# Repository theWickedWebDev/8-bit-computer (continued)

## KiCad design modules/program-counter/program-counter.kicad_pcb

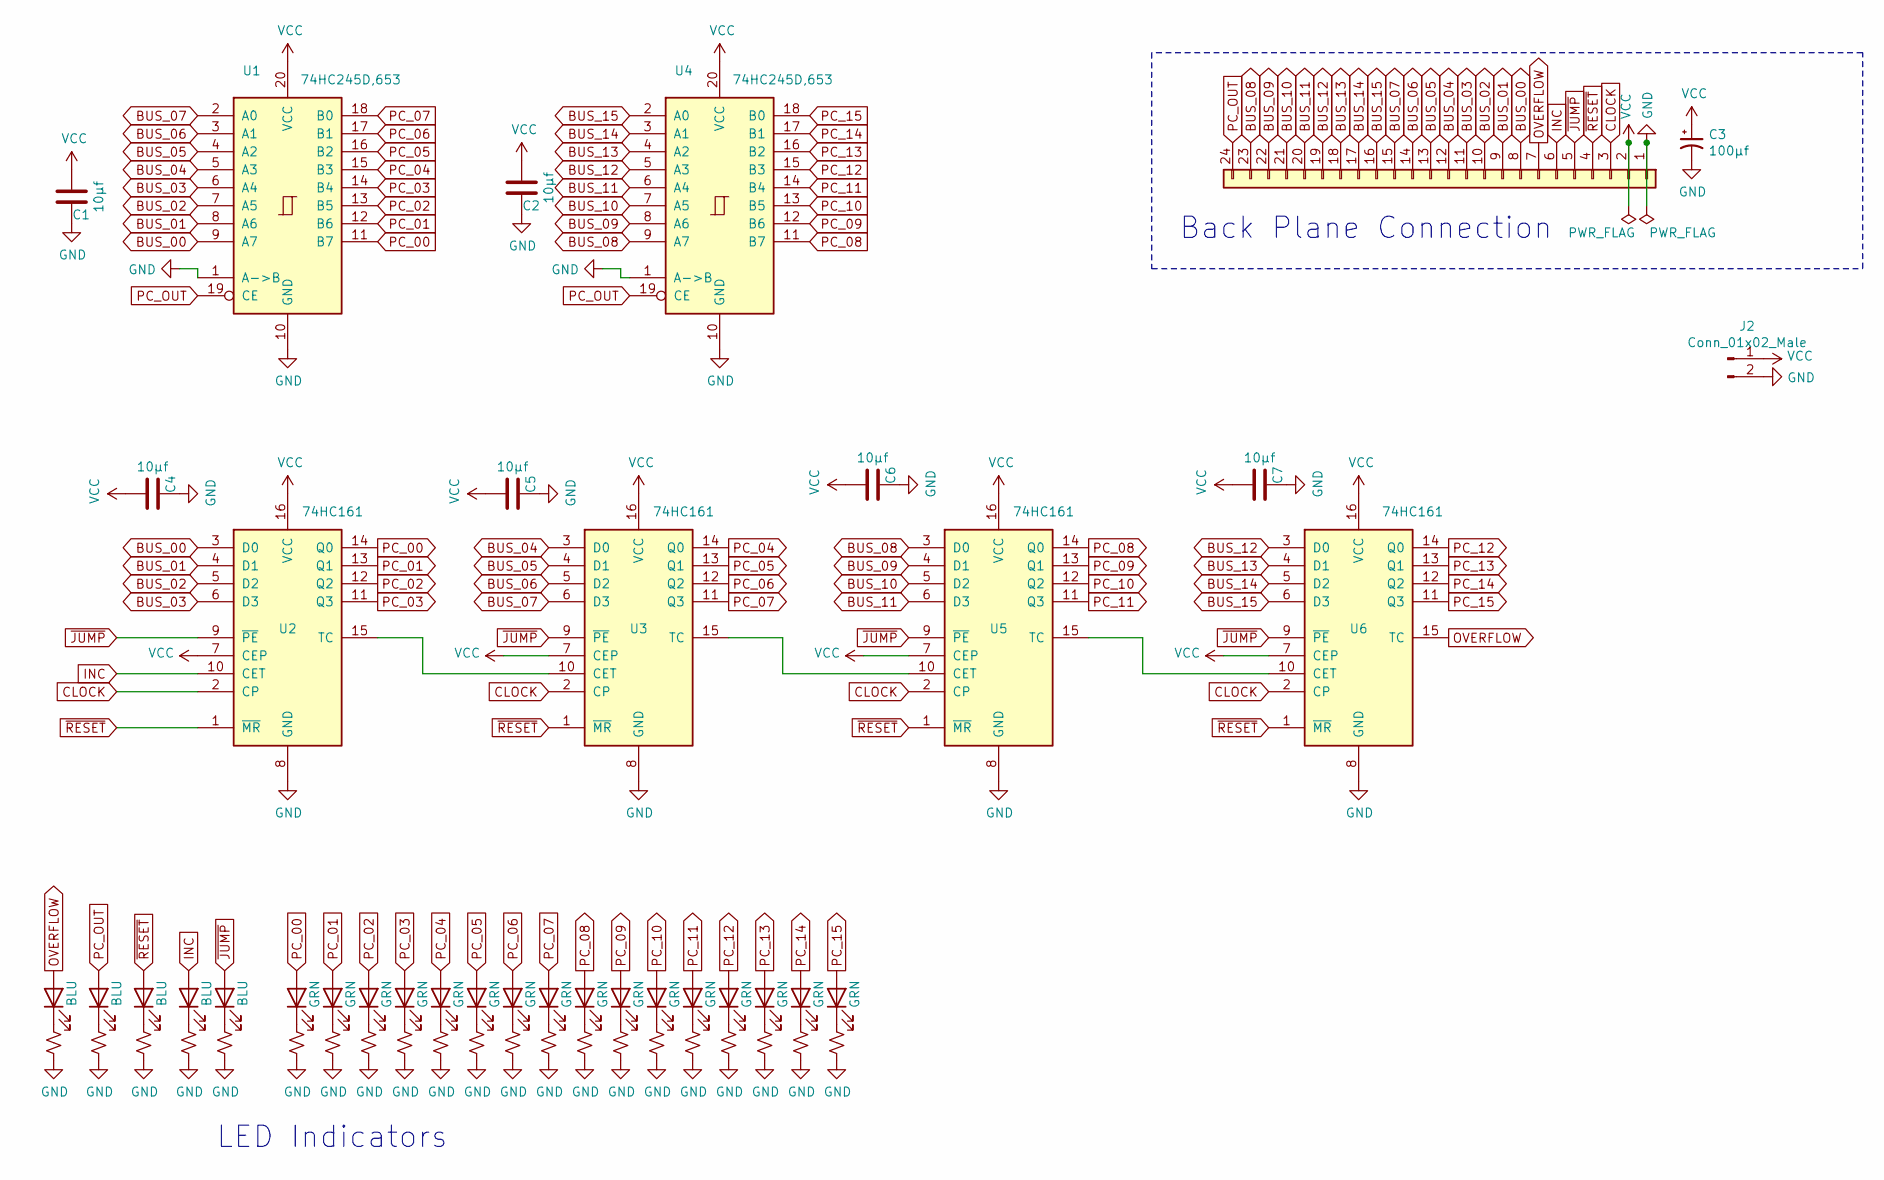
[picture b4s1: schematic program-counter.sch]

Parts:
C1, C2, C4, C5, C6, C7: CL05A106MQ5NUNC; C_0402_1005Metric; JLCPCB C15525
C3: SMD-ECAP-5x5.8; CP_Elec_5x5.8; JLCPCB C140924
D1, D2, D3, D4, D21: 19-217/BHC-ZL1M2RY/3T; LED_0603_1608Metric; JLCPCB C72041
D5, D6, D7, D8, D9, D10, D11, D12, D13, D14, D15, D16, D17, D18, D19, D20: 19-217/GHC-YR1S2/3T; LED_0603_1608Metric; JLCPCB C72043
J1: Conn_01x24; PinHeader_1x24_P2.54mm_Vertical
J2: Conn_01x02_Male; PinHeader_1x02_P2.54mm_Vertical
R1, R2, R3, R4, R5, R6, R7, R8, R9, R10, R11, R12, R13, R14, R15, R16, R17, R18, R19, R20, R21: 0402WGF1001TCE; R_0402_1005Metric; JLCPCB C11702
U1, U4: 74HC245D,653; SO-20_12.8x7.5mm_P1.27mm; JLCPCB C5625
U2, U3, U5, U6: SN74HC161DR; SOIC-16_3.9x9.9mm_P1.27mm

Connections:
BUS_00: J1.8, U1.9 (A7), U2.3 (D0)
BUS_01: J1.9, U1.8 (A6), U2.4 (D1)
BUS_02: J1.10, U1.7 (A5), U2.5 (D2)
BUS_03: J1.11, U1.6 (A4), U2.6 (D3)
BUS_04: J1.12, U1.5 (A3), U3.3 (D0)
BUS_05: J1.13, U1.4 (A2), U3.4 (D1)
BUS_06: J1.14, U1.3 (A1), U3.5 (D2)
BUS_07: J1.15, U1.2 (A0), U3.6 (D3)
BUS_08: J1.23, U4.9 (A7), U5.3 (D0)
BUS_09: J1.22, U4.8 (A6), U5.4 (D1)
BUS_10: J1.21, U4.7 (A5), U5.5 (D2)
BUS_11: J1.20, U4.6 (A4), U5.6 (D3)
BUS_12: J1.19, U4.5 (A3), U6.3 (D0)
BUS_13: J1.18, U4.4 (A2), U6.4 (D1)
BUS_14: J1.17, U4.3 (A1), U6.5 (D2)
BUS_15: J1.16, U4.2 (A0), U6.6 (D3)
CLOCK: J1.3, U2.2 (CP), U3.2 (CP), U5.2 (CP), U6.2 (CP)
GND: C1.2, C2.2, C3.2, C4.2, C5.2, C6.2, C7.2, J1.1, J2.2, R1.2, R2.2, R3.2, R4.2, R5.2, R6.2, R7.2, R8.2, R9.2, R10.2, R11.2, R12.2, R13.2, R14.2, R15.2, R16.2, R17.2, R18.2, R19.2, R20.2, R21.2, U1.1 (A->B), U1.10 (GND), U2.8 (GND), U3.8 (GND), U4.1 (A->B), U4.10 (GND), U5.8 (GND), U6.8 (GND)
INC: D3.2 (A), J1.6, U2.10 (CET)
unnamed: D1.1 (K), R1.1
unnamed: D2.1 (K), R2.1
unnamed: D3.1 (K), R3.1
unnamed: D4.1 (K), R4.1
unnamed: D5.1 (K), R5.1
unnamed: D6.1 (K), R6.1
unnamed: D7.1 (K), R7.1
unnamed: D8.1 (K), R8.1
unnamed: D9.1 (K), R9.1
unnamed: D10.1 (K), R10.1
unnamed: D11.1 (K), R11.1
unnamed: D12.1 (K), R12.1
unnamed: D13.1 (K), R13.1
unnamed: D14.1 (K), R14.1
unnamed: D15.1 (K), R15.1
unnamed: D16.1 (K), R16.1
unnamed: D17.1 (K), R17.1
unnamed: D18.1 (K), R18.1
unnamed: D19.1 (K), R19.1
unnamed: D20.1 (K), R20.1
unnamed: D21.1 (K), R21.1
unnamed: U2.15 (TC), U3.10 (CET)
unnamed: U3.15 (TC), U5.10 (CET)
unnamed: U5.15 (TC), U6.10 (CET)
OVERFLOW: D21.2 (A), J1.7, U6.15 (TC)
PC_00: D5.2 (A), U1.11 (B7), U2.14 (Q0)
PC_01: D6.2 (A), U1.12 (B6), U2.13 (Q1)
PC_02: D7.2 (A), U1.13 (B5), U2.12 (Q2)
PC_03: D8.2 (A), U1.14 (B4), U2.11 (Q3)
PC_04: D9.2 (A), U1.15 (B3), U3.14 (Q0)
PC_05: D10.2 (A), U1.16 (B2), U3.13 (Q1)
PC_06: D11.2 (A), U1.17 (B1), U3.12 (Q2)
PC_07: D12.2 (A), U1.18 (B0), U3.11 (Q3)
PC_08: D13.2 (A), U4.11 (B7), U5.14 (Q0)
PC_09: D14.2 (A), U4.12 (B6), U5.13 (Q1)
PC_10: D15.2 (A), U4.13 (B5), U5.12 (Q2)
PC_11: D16.2 (A), U4.14 (B4), U5.11 (Q3)
PC_12: D17.2 (A), U4.15 (B3), U6.14 (Q0)
PC_13: D18.2 (A), U4.16 (B2), U6.13 (Q1)
PC_14: D19.2 (A), U4.17 (B1), U6.12 (Q2)
PC_15: D20.2 (A), U4.18 (B0), U6.11 (Q3)
PC_OUT: D2.2 (A), J1.24, U1.19 (CE), U4.19 (CE)
VCC: C1.1, C2.1, C3.1, C4.1, C5.1, C6.1, C7.1, J1.2, J2.1, U1.20 (VCC), U2.7 (CEP), U2.16 (VCC), U3.7 (CEP), U3.16 (VCC), U4.20 (VCC), U5.7 (CEP), U5.16 (VCC), U6.7 (CEP), U6.16 (VCC)
~JUMP: D4.2 (A), J1.5, U2.9 (~PE), U3.9 (~PE), U5.9 (~PE), U6.9 (~PE)
~RESET: D1.2 (A), J1.4, U2.1 (~MR), U3.1 (~MR), U5.1 (~MR), U6.1 (~MR)

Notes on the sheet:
Back Plane Connection
LED Indicators

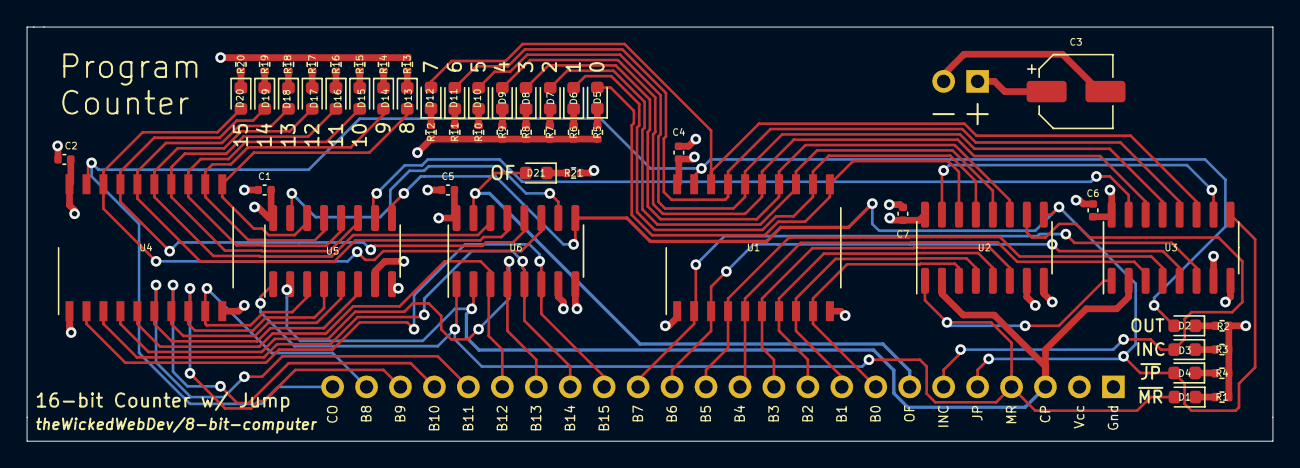
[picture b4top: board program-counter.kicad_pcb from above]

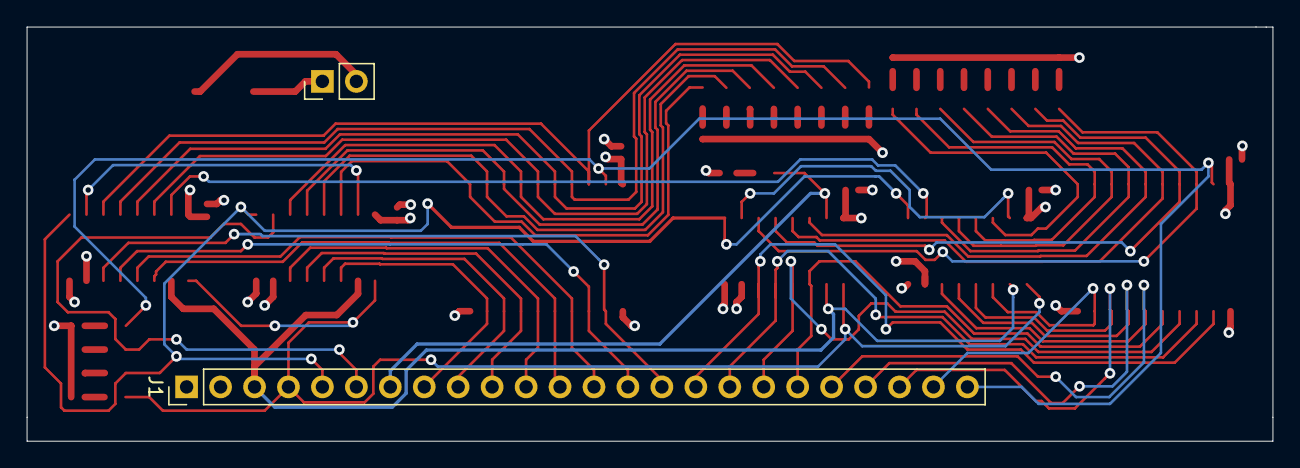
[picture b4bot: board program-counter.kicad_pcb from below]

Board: 4 copper layers, 93.2 x 31.0 mm, 57 parts (2 on the bottom side), 64 nets.

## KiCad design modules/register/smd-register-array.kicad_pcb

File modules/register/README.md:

# General Storage Register

### Status

### Board

### Details

### Control Truth Table

| MS | LS | BS | EN | CP | Mn | Ln | Bn |                                            |
|:--:|:--:|:--:|:--:|:--:|:--:|:--:|:--:|:------------------------------------------:|
|  0 |  0 |  0 |  1 | RE |  x |  x |  x | Latches Data from Main Data BUS            |
|  1 |  1 |  0 |  0 |  x |  x |  x | Qn | Outputs register contents to Main Data BUS |
|  1 |  0 |  1 |  0 |  x |  x | Qn |  x | Outputs register contents to LSB BUS       |
|  0 |  1 |  1 |  0 |  x | Qn |  x |  x | Outputs register contents to MSB BUS       |
|  0 |  0 |  0 |  0 |  x | Qn | Qn | Qn | Outputs register to all BUS's              |

`BS` - (Active Low) Output to Main Data BUS

`MS` - (Active Low) Output to MSB BUS

`MS` - (Active Low) Output to LSB BUS

`EN` - Enable load on register. Latches on the rising edge of the clock

`CP` - Clock Pulse

`M[0..7]` - BUS output for MSB

`L[0..7]` - BUS output for LSB

`B[0..7]` - BUS output for Main Data Bus

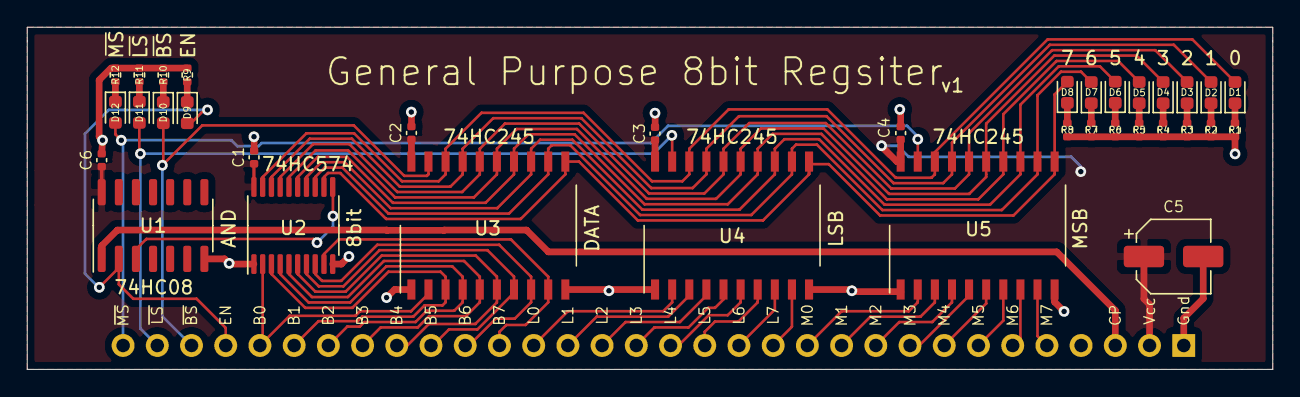
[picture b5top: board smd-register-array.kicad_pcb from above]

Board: 2 copper layers, 92.5 x 25.4 mm, 36 parts (1 on the bottom side), 52 nets.

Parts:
C1, C2, C3, C4, C6: CL05A106MQ5NUNC; C_0402_1005Metric
C5: SMD-ECAP-5x5.8; CP_Elec_5x5.8
D1, D2, D3, D4, D5, D6, D7, D8: 19-217/GHC-YR1S2/3T; LED_0603_1608Metric
D9, D10, D11, D12: 19-217/BHC-ZL1M2RY/3T; LED_0603_1608Metric
J1: Conn_01x32; PinHeader_1x32_P2.54mm_Vertical
R1, R2, R3, R4, R5, R6, R7, R8, R9, R10, R11, R12: 0402WGF1001TCE; R_0402_1005Metric
U1: 74HC08D,653; SOIC-14_3.9x8.7mm_P1.27mm
U2: 74HC574PW,118; TSSOP-20_4.4x6.5mm_P0.65mm
U3, U4, U5: 74HC245D,653; SO-20_12.8x7.5mm_P1.27mm

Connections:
/BUS_OUT: D10.2, J1.30, U3.19
/EN: D9.2, J1.29, U1.2
/LSB_OUT: D11.2, J1.31, U4.19
/MSB_OUT: D12.2, J1.32, U5.19
A0: D1.2, U2.19, U3.18, U4.18, U5.18
A1: D2.2, U2.18, U3.17, U4.17, U5.17
A2: D3.2, U2.17, U3.16, U4.16, U5.16
A3: D4.2, U2.16, U3.15, U4.15, U5.15
A4: D5.2, U2.15, U3.14, U4.14, U5.14
A5: D6.2, U2.14, U3.13, U4.13, U5.13
A6: D7.2, U2.13, U3.12, U4.12, U5.12
A7: D8.2, U2.12, U3.11, U4.11, U5.11
BUS_00: J1.28, U2.2, U3.2
BUS_01: J1.27, U2.3, U3.3
BUS_02: J1.26, U2.4, U3.4
BUS_03: J1.25, U2.5, U3.5
BUS_04: J1.24, U2.6, U3.6
BUS_05: J1.23, U2.7, U3.7
BUS_06: J1.22, U2.8, U3.8
BUS_07: J1.21, U2.9, U3.9
CLOCK: J1.3, U1.1
GND: C1.2, C2.2, C3.2, C4.2, C5.2, C6.2, J1.1, R1.2, R2.2, R3.2, R4.2, R5.2, R6.2, R7.2, R8.2, R9.2, R10.2, R11.2, R12.2, U1.7, U2.1, U2.10, U3.1, U3.10, U4.1, U4.10, U5.1, U5.10
LSB_00: J1.20, U4.2
LSB_01: J1.19, U4.3
LSB_02: J1.18, U4.4
LSB_03: J1.17, U4.5
LSB_04: J1.16, U4.6
LSB_05: J1.15, U4.7
LSB_06: J1.14, U4.8
LSB_07: J1.13, U4.9
MSB_00: J1.12, U5.2
MSB_01: J1.11, U5.3
MSB_02: J1.10, U5.4
MSB_03: J1.9, U5.5
MSB_04: J1.8, U5.6
MSB_05: J1.7, U5.7
MSB_06: J1.6, U5.8
MSB_07: J1.5, U5.9
unnamed: D1.1, R1.1
unnamed: D2.1, R2.1
unnamed: D3.1, R3.1
unnamed: D4.1, R4.1
unnamed: D5.1, R5.1
unnamed: D6.1, R6.1
unnamed: D7.1, R7.1
unnamed: D8.1, R8.1
unnamed: D9.1, R9.1
unnamed: D10.1, R10.1
unnamed: D11.1, R11.1
unnamed: D12.1, R12.1
unnamed: U1.3, U2.11
VCC: C1.1, C2.1, C3.1, C4.1, C5.1, C6.1, J1.2, U1.14, U2.20, U3.20, U4.20, U5.20

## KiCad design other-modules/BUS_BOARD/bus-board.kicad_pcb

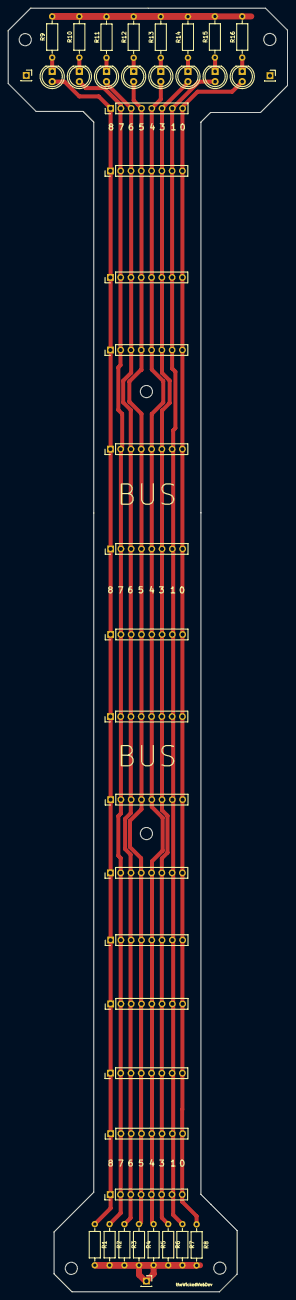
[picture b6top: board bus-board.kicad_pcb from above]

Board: 2 copper layers, 69.0 x 317.0 mm, 42 parts (0 on the bottom side), 17 nets.

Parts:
D1, D2, D3, D4, D5, D6, D7, D8: LED; LED_D5.0mm
J1, J2, J3, J4, J5, J6, J7, J8, J9, J10, J12, J13, J14, J15, J16: Conn_01x08; PinHeader_1x08_P2.54mm_Vertical
J11, J17, J18: Conn_01x01; PinSocket_1x01_P2.54mm_Vertical
R1, R2, R3, R4, R5, R6, R7, R8, R9, R10, R11, R12, R13, R14, R15, R16: R_Small_US; R_Axial_DIN0207_L6.3mm_D2.5mm_P10.16mm_Horizontal

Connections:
GND: J11.1, J17.1, J18.1, R1.2, R2.2, R3.2, R4.2, R5.2, R6.2, R7.2, R8.2, R9.2, R10.2, R11.2, R12.2, R13.2, R14.2, R15.2, R16.2
unnamed: D1.1, R9.1
unnamed: D1.2, J1.1, J2.1, J3.1, J4.1, J5.1, J6.1, J7.1, J8.1, J9.1, J10.1, J12.1, J13.1, J14.1, J15.1, J16.1, R1.1
unnamed: D2.1, R10.1
unnamed: D2.2, J1.2, J2.2, J3.2, J4.2, J5.2, J6.2, J7.2, J8.2, J9.2, J10.2, J12.2, J13.2, J14.2, J15.2, J16.2, R2.1
unnamed: D3.1, R11.1
unnamed: D3.2, J1.3, J2.3, J3.3, J4.3, J5.3, J6.3, J7.3, J8.3, J9.3, J10.3, J12.3, J13.3, J14.3, J15.3, J16.3, R3.1
unnamed: D4.1, R12.1
unnamed: D4.2, J1.4, J2.4, J3.4, J4.4, J5.4, J6.4, J7.4, J8.4, J9.4, J10.4, J12.4, J13.4, J14.4, J15.4, J16.4, R4.1
unnamed: D5.1, R13.1
unnamed: D5.2, J1.5, J2.5, J3.5, J4.5, J5.5, J6.5, J7.5, J8.5, J9.5, J10.5, J12.5, J13.5, J14.5, J15.5, J16.5, R5.1
unnamed: D6.1, R14.1
unnamed: D6.2, J1.6, J2.6, J3.6, J4.6, J5.6, J6.6, J7.6, J8.6, J9.6, J10.6, J12.6, J13.6, J14.6, J15.6, J16.6, R6.1
unnamed: D7.1, R15.1
unnamed: D7.2, J1.7, J2.7, J3.7, J4.7, J5.7, J6.7, J7.7, J8.7, J9.7, J10.7, J12.7, J13.7, J14.7, J15.7, J16.7, R7.1
unnamed: D8.1, R16.1
unnamed: D8.2, J1.8, J2.8, J3.8, J4.8, J5.8, J6.8, J7.8, J8.8, J9.8, J10.8, J12.8, J13.8, J14.8, J15.8, J16.8, R8.1
